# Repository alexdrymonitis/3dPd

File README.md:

# 3dPd

This repository hosts the code, schematics, and circuit board designs made in Kicad, for a hardware digital modular synthesizer. The audio is programmed in Pure Data and the hardware control in the Arduino language.
This synthesizer is supposed to run on a Raspberry Pi 3 and a Teensy3.2. You're welcome to use any other hardware you like, but this specific hardware is supported and explained here.

## Note about the Arduino code

Go to the Arduino_code directory and read the README.txt file first. That should give you enough information about the Arduino code. Do that before you start reading the Pd patches.

## Note about the Pd patches

The heart of this project is the modular_synthesizer.pd patch. Open it and you'll see some other abstractions in there. Go into the [pd modules] sub-patch and look inside.
Each module must have its own abstraction. There are some tutorial module abstractions which show you how to build your own. Open them and read them carefully.

There's also a debug.pd patch which helps with debugging by showing input from the Teensy and printing various message concerning module connections and LED states.

### Dependencies

This project uses the following external libraries:  
zexy  
comport  
iemmatrix  
iemguts  
ggee  
list-abs  
tabreceive_mult~  

The first five libraries are being installed with "apt-get" and the last two are installed through Deken (In Pd got to Help -> Find externals and type these two names -one at a time-, the highlighted version(s) is good for your system).

Pd-0.47.0 or higher is required.

## General note

I'll upload a wiki with instructions for creating the hardware of a module and the whole system. It's in my TODO list, which will hopefully happen in the near future.
You can watch a demo video of the synthesizer here https://www.youtube.com/watch?v=HD13bDPyBWA

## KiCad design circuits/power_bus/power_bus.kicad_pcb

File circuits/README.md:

# Circuit designs, schematics, and gerber files directory

This README file provides only very basic information about the circuits. I'm planning on releasing a wiki on how to build hardware modules in the next few days.

## Generic note about this directory

In this directory you'll find all the circuits used in this modular synthesizer. It's six circuits in total, each in its own directory. They have been designed in Kicad and all the necessary files are here. Each directory includes a README file which states which extra built-in libraries have been used. The ones I have made especially for these circuits are not mentioned in the README since their directories (library/ and .pretty/) are included here. The directories also include the gerber files for sending them to a manufacturer, plus a .png file for each side (in case of double-sided boards) in case you want to DIY etch it, and a .pdf with the schematic.

If you've never used Kicad before and want to modify any of the circuits, I recommend to read some of the tutorials provided from Kicad's website. This tutorial was very useful for me http://kicad-pcb.org/help/documentation/#_getting_started. If you just want to have them manufactured, you can send the gerber files straight to a manufacturer.

## Note about the circuits

### Parts

There's a parts list in every circuit directory with all the parts of that circuit. Where I thought it was necessary, I provide a link to the datasheet of that part. Parts are identified by their annotation from the schematic. Consult the board design (Pcbnew) to make sure which part goes where.

### Orientation of parts

The orientation of the ICs on the "module_generic_top_board" is not defined by the shape of the footprint part but by the pin numbering. If you're not sure, open Pcbnew, go to View -> 3D Viewer and there you can see the notches of the ICs which indicate their orientation.
The orientation of the IDC connectors can be defined by the pin numbering. On an actual IDC connector, you can see a small arrow at the left side of the notch. This arrow indicates that the left-most pin on the side of the notch, is pin number 1.

### Concerning manufacturing

The boards "module_generic_top_board" and "module_generic_bottom_board" are needed for every module. I would suggest to order these from a manufacturer instead of etching them your self many times. The "module_specific_board" and "module_specific_board"2 are just examples of how you can connect your parts to the generic boards (this will be analyzed in the upcoming wiki). There are two of those because I wanted to provide both orientations for the potentiometers, because of the knobs one can find (they are D-shaped knobs, so orientation is rather important). You can order few of these as well, since it is designed in such a way that can host many different layouts.

The "power_bus", "power_distributor", and "teensy_motherboard" are designed as single-side circuit boards (with the "teensy_motherboard" using three jumpers, the "power_bus" only one, and the "power_distributor" none) so that it's easier to etch them yourself. You'll need only one per board (unless you want to build more than 16 modules, then you'll need a second "power_bus", explained in the upcoming wiki), so ordering those from a manufacturer might not work out.

Eacn board has a .pdf file which you can print for DIY etching, either with toner transfer or with photo-resistant boards. The "module_generic_top_board", "module_generic_bottom_board", and "module_specific_board" have two .pdf, one for each side, while the rest three have only one .pdf file.

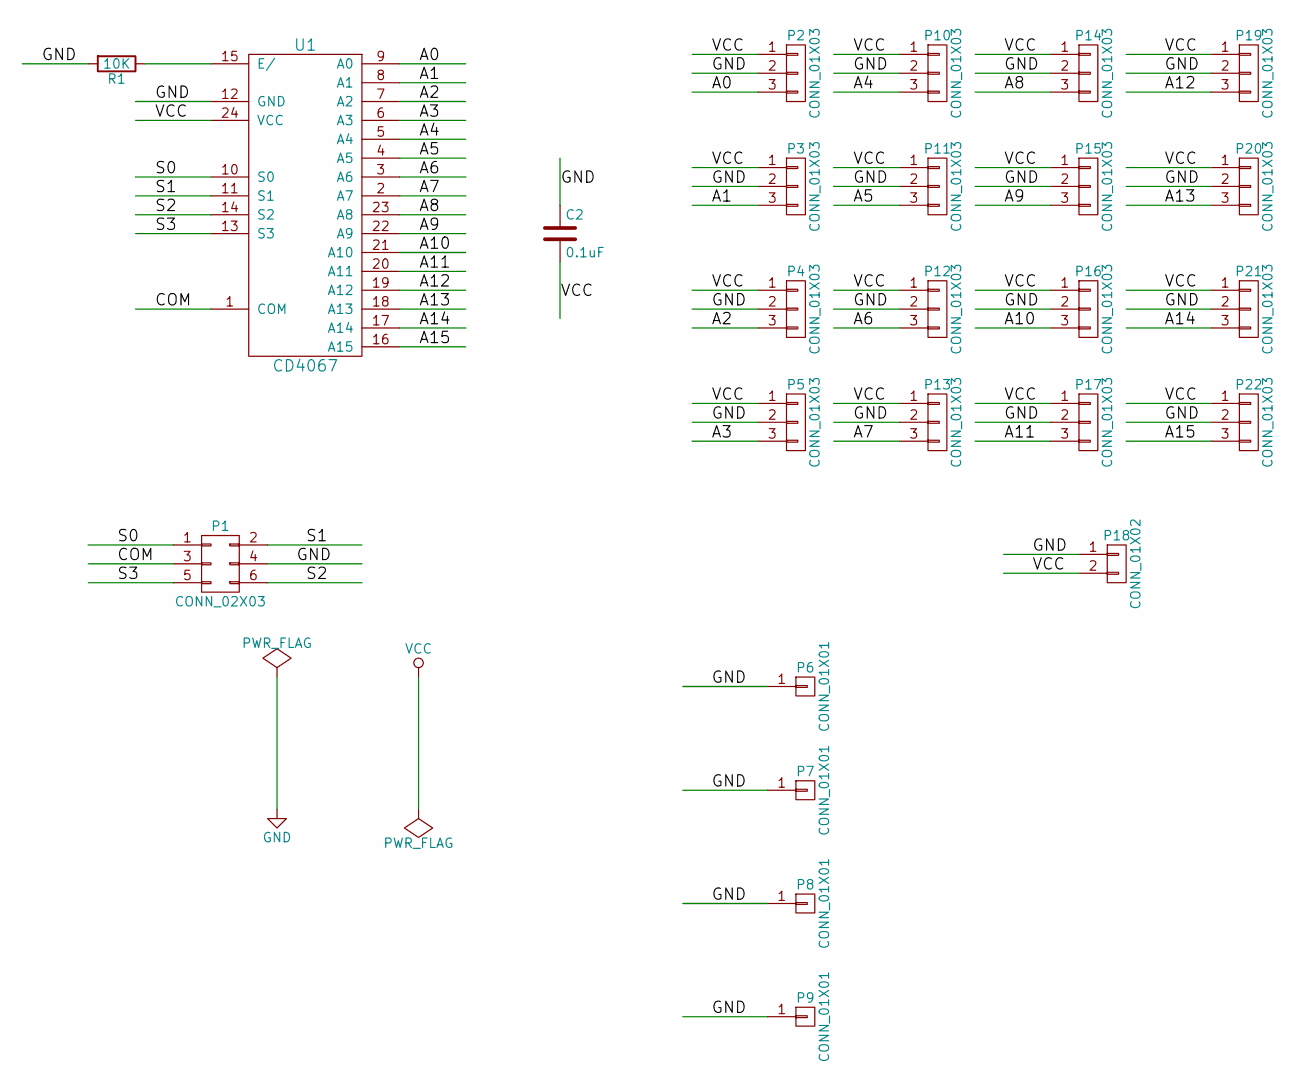
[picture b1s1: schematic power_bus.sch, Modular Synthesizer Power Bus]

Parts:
C2: 0.1uF; C_Disc_D3_P2.5
P1: CONN_02X03; Pin_Header_Straight_2x03
P2, P3, P4, P5, P10, P11, P12, P13, P14, P15, P16, P17, P19, P20, P21, P22: CONN_01X03; Connectors_JST_B3B-PH-K
P6, P7, P8, P9: CONN_01X01; hole
P18: CONN_01X02; bornier2
R1: 10K; R3
U1: CD4067

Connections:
/A0: P2.3, U1.9 (A0)
/A1: P3.3, U1.8 (A1)
/A2: P4.3, U1.7 (A2)
/A3: P5.3, U1.6 (A3)
/A4: P10.3, U1.5 (A4)
/A5: P11.3, U1.4 (A5)
/A6: P12.3, U1.3 (A6)
/A7: P13.3, U1.2 (A7)
/A8: P14.3, U1.23 (A8)
/A9: P15.3, U1.22 (A9)
/A10: P16.3, U1.21 (A10)
/A11: P17.3, U1.20 (A11)
/A12: P19.3, U1.19 (A12)
/A13: P20.3, U1.18 (A13)
/A14: P21.3, U1.17 (A14)
/A15: P22.3, U1.16 (A15)
/COM: P1.3, U1.1 (COM)
/S0: P1.1, U1.10 (S0)
/S1: P1.2, U1.11 (S1)
/S2: P1.6, U1.14 (S2)
/S3: P1.5, U1.13 (S3)
GND: C2.1, P1.4, P2.2, P3.2, P4.2, P5.2, P6.1, P7.1, P8.1, P9.1, P10.2, P11.2, P12.2, P13.2, P14.2, P15.2, P16.2, P17.2, P18.1, P19.2, P20.2, P21.2, P22.2, R1.2, U1.12 (GND)
unnamed: R1.1, U1.15 (E‭‎/)
VCC: C2.2, P2.1, P3.1, P4.1, P5.1, P10.1, P11.1, P12.1, P13.1, P14.1, P15.1, P16.1, P17.1, P18.2, P19.1, P20.1, P21.1, P22.1, U1.24 (VCC)

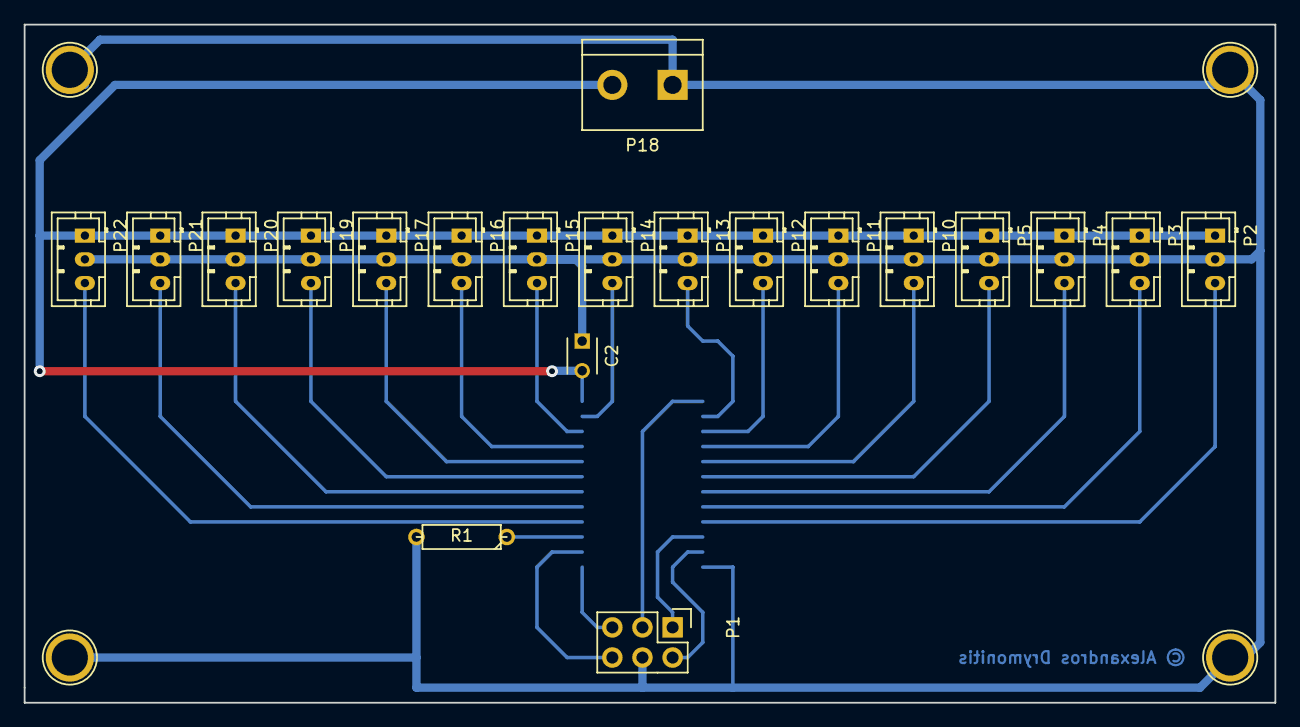
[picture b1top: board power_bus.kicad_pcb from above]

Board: 2 copper layers, 105.4 x 57.2 mm, 25 parts (1 on the bottom side), 24 nets.

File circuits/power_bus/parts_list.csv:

Reference, Value, Type, Datasheet
U1,CD4067,16-channel Analog Multiplexer 4067,https://www.sparkfun.com/datasheets/IC/CD74HC4067.pdf
P2,CONN_01X03,JST PH Connector Male Angled 3-pin,
P10,CONN_01X03,JST PH Connector Male Angled 3-pin,
P14,CONN_01X03,JST PH Connector Male Angled 3-pin,
P19,CONN_01X03,JST PH Connector Male Angled 3-pin,
P3,CONN_01X03,JST PH Connector Male Angled 3-pin,
P11,CONN_01X03,JST PH Connector Male Angled 3-pin,
P15,CONN_01X03,JST PH Connector Male Angled 3-pin,
P20,CONN_01X03,JST PH Connector Male Angled 3-pin,
P4,CONN_01X03,JST PH Connector Male Angled 3-pin,
P12,CONN_01X03,JST PH Connector Male Angled 3-pin,
P16,CONN_01X03,JST PH Connector Male Angled 3-pin,
P21,CONN_01X03,JST PH Connector Male Angled 3-pin,
P5,CONN_01X03,JST PH Connector Male Angled 3-pin,
P13,CONN_01X03,JST PH Connector Male Angled 3-pin,
P17,CONN_01X03,JST PH Connector Male Angled 3-pin,
P22,CONN_01X03,JST PH Connector Male Angled 3-pin,
P1,CONN_02X03,IDC Connector Male 2x3 Straight,
C2,0.1uF,Capacitor Ceramic Unpolarized,
P18,CONN_01X02,Screw Terminal 2-pin 5mm Pitch,
R1,10K,Resistor,

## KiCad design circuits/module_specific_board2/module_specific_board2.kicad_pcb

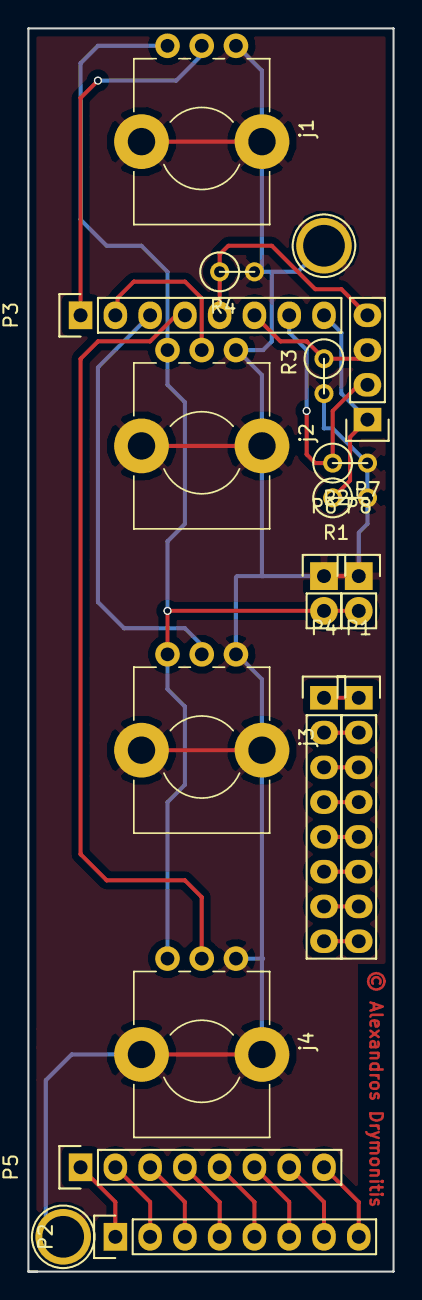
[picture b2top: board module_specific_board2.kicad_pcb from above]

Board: 2 copper layers, 26.7 x 90.8 mm, 18 parts (0 on the bottom side), 26 nets.

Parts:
P1, P2, P3, P4, P5: CONN_01X08; Pin_Header_Straight_1x08
P6, P8: CONN_01X02; Pin_Header_Straight_1x02
P7: CONN_01X04; Pin_Header_Straight_1x04
P9, P10: CONN_01X01; hole
R1, R2, R3, R4: 10K; R1
j1, j2, j3, j4: ALPSpot097; Potentiometer_Alps_RK09K_Horizontal

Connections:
/MUX5: P3.5, P7.4, R4.1
/MUX6: P3.6, P7.3, R3.1
/MUX7: P3.7, P7.2, R2.1
/MUX8: P3.8, P7.1, R1.1
/POT1: P3.1, j1.2
/POT2: P3.2, j2.2
/POT3: P3.3, j3.2
/POT4: P3.4, j4.2
GND: P6.1, P8.1, P9.1, P10.1, R1.2, R2.2, R3.2, R4.2, j1.0, j1.3, j2.0, j2.3, j3.0, j3.3, j4.0, j4.3
unnamed: P1.1, P4.1
unnamed: P1.2, P4.2
unnamed: P1.3, P4.3
unnamed: P1.4, P4.4
unnamed: P1.5, P4.5
unnamed: P1.6, P4.6
unnamed: P1.7, P4.7
unnamed: P1.8, P4.8
unnamed: P2.1, P5.1
unnamed: P2.2, P5.2
unnamed: P2.3, P5.3
unnamed: P2.4, P5.4
unnamed: P2.5, P5.5
unnamed: P2.6, P5.6
unnamed: P2.7, P5.7
unnamed: P2.8, P5.8
VCC: P6.2, P8.2, j1.1, j2.1, j3.1, j4.1

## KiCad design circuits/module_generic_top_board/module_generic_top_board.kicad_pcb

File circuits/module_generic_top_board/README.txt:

This circuit contains the Connectors_JST_PH.pretty footprint library in the project specific libraries, from ${KISYSMOD}/Connectors_JST_PH.pretty

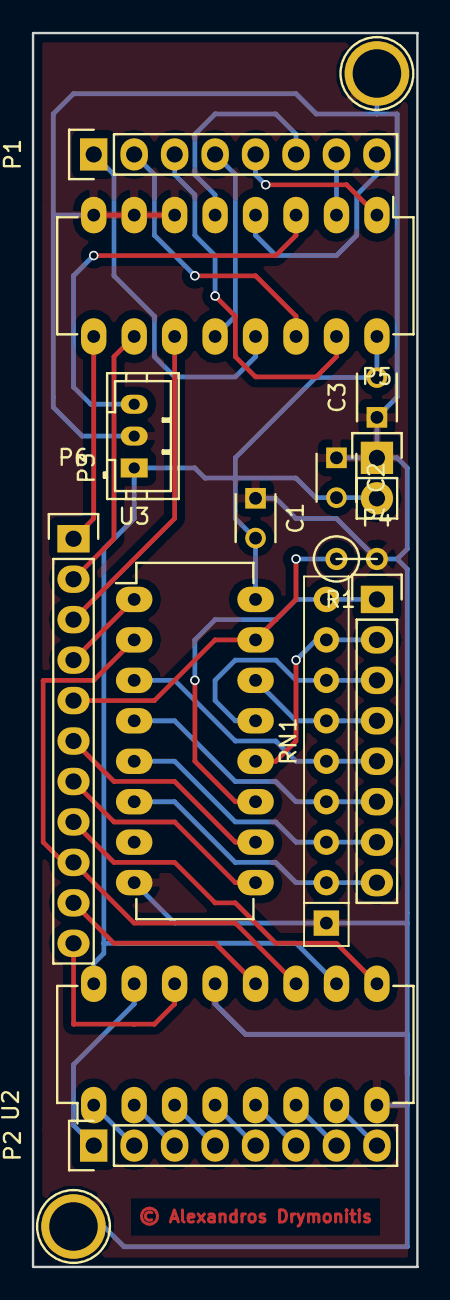
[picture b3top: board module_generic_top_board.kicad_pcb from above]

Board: 2 copper layers, 24.1 x 77.5 mm, 16 parts (0 on the bottom side), 38 nets.

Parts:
C1, C2, C3: 0.1uF; C_Disc_D3_P2.5
P1, P2, P4: CONN_01X08; Pin_Header_Straight_1x08
P3: CONN_01X03; Connectors_JST_B3B-PH-K
P5: CONN_01X02; Pin_Header_Straight_1x02
P6: CONN_01X11; Pin_Header_Straight_1x11
P7, P8: CONN_01X01; hole
R1: 10K; R1
RN1: 10K; R_Array_SIP9
U1: 4051; DIP-16_W7.62mm_LongPads
U2: 74HC595; DIP-16_W7.62mm_LongPads
U3: 74HC165; DIP-16_W7.62mm_LongPads

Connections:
/MUXA: P6.3, U1.11
/MUXB: P6.2, U1.10
/MUXC: P6.1, U1.9
/QH: P6.7, U3.9
/QH/: P6.8, U2.9
/RCLK: P6.10, U2.12
/SH/LD: P6.4, U3.1
/SHIFTIN_A: P4.1, RN1.9, U3.11
/SHIFTIN_B: P4.2, RN1.8, U3.12
/SHIFTIN_C: P4.3, RN1.7, U3.13
/SHIFTIN_D: P4.4, RN1.6, U3.14
/SHIFTIN_E: P4.5, RN1.5, U3.3
/SHIFTIN_F: P4.6, RN1.4, U3.4
/SHIFTIN_G: P4.7, RN1.3, U3.5
/SHIFTIN_H: P4.8, RN1.2, U3.6
/SHIFTIN_SER: P6.6, U3.10
/SHIFTOUT_SER: P6.11, U2.14
/SHIFT_INH: P6.5, R1.1, U3.15
/SRCLK: P6.9, U2.11, U3.2
GND: C1.1, C2.1, C3.1, P3.2, P5.1, P7.1, P8.1, R1.2, RN1.1, U1.6, U1.7, U1.8, U2.8, U2.13, U3.8
unnamed: P1.1, U1.13
unnamed: P1.2, U1.14
unnamed: P1.3, U1.15
unnamed: P1.4, U1.12
unnamed: P1.5, U1.1
unnamed: P1.6, U1.5
unnamed: P1.7, U1.2
unnamed: P1.8, U1.4
unnamed: P2.1, U2.15
unnamed: P2.2, U2.1
unnamed: P2.3, U2.2
unnamed: P2.4, U2.3
unnamed: P2.5, U2.4
unnamed: P2.6, U2.5
unnamed: P2.7, U2.6
unnamed: P2.8, U2.7
unnamed: P3.3, U1.3
VCC: C1.2, C2.2, C3.2, P3.1, P5.2, U1.16, U2.10, U2.16, U3.16

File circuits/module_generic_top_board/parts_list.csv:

Reference, Value,Type, Datasheet
C1,0.1uF,Capacitor Ceramic Unpolarized,
C2,0.1uF,Capacitor Ceramic Unpolarized,
C3,0.1uF,Capacitor Ceramic Unpolarized,
RR1,10K,Resistor Network 8 + 1,
P2,CONN_01X08,Female Header Straight 8-pin 0.1 Inch,
P1,CONN_01X08,Female Header Straight 8-pin 0.1 Inch,
P4,CONN_01X08,Female Header Straight 8-pin 0.1 Inch,
P5,CONN_01X02,Female Header Straight 2-pin 0.1 Inch,
P6,CONN_01X11,Female Header Straight 11-pin 0.1 Inch,
P3,CONN_01X03,JST PH Connector Male Angled 3-pin,
U3,74HC165,8-bit Input Shift Register,https://cdn.sparkfun.com/datasheets/BreakoutBoards/sn54hc165.pdf
U2,74HC595,8-bit Output Shift Register,http://www.ti.com/lit/ds/symlink/sn74hc595.pdf
U1,4051,8-channel Analog Multiplexer,http://grobotronics.com/images/datasheets/schs354a.pdf
R1,10K,Resistor,

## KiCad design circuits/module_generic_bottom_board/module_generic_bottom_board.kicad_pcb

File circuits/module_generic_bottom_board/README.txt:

This circuit contains the switches schematic parts library from /usr/share/kicak/library

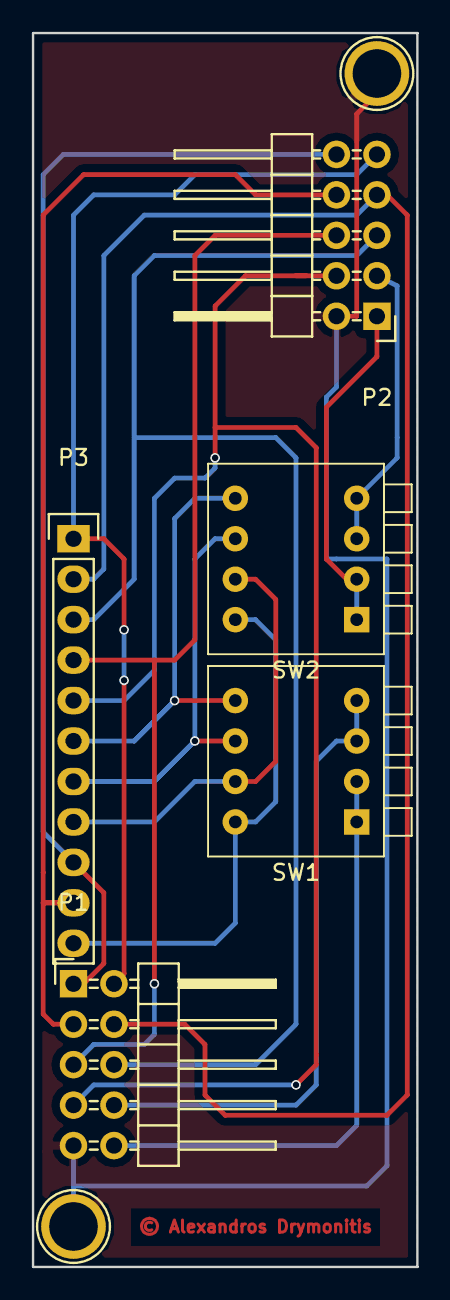
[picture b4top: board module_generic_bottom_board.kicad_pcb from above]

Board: 2 copper layers, 24.1 x 77.5 mm, 7 parts (0 on the bottom side), 16 nets.

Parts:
P1, P2: CONN_02X05; Pin_Header_Angled_2x05
P3: CONN_01X11; Pin_Header_Straight_1x11
P4, P5: CONN_01X01; hole
SW1, SW2: SW_DIP_x04; SW_DIP_x4_W7.62mm_Piano

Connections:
/MUXA: P1.6, P2.5, P3.3
/MUXB: P1.4, P2.7, P3.2
/MUXC: P1.2, P2.9, P3.1
/QH: P3.7, SW1.6, SW2.6
/QH/: P3.8, SW1.7, SW2.7
/RCLK: P1.3, P2.8, P3.10
/SH/LD: P1.5, P2.6, P3.4
/SHIFTIN_SER: P3.6, SW1.5, SW2.5
/SHIFTOUT_SER: P3.11, SW1.8, SW2.8
/SHIFT_INH: P1.7, P2.4, P3.5
/SRCLK: P1.1, P2.10, P3.9
/SW1_12: P1.10, SW1.1, SW1.2
/SW1_34: P1.8, SW1.3, SW1.4
/SW2_12: P2.1, SW2.1, SW2.2
/SW2_34: P2.3, SW2.3, SW2.4
GND: P1.9, P2.2, P4.1, P5.1

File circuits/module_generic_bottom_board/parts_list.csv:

Reference, Value, Type
P2,CONN_02X05,IDC Connector 2x5 Angled
P1,CONN_02X05,IDC Connector 2x5 Angled
P3,CONN_01X11,Header Male 11-pin Straight
S1,SW_DIP_x4,DIP Switch 4-position Piano Type
S2,SW_DIP_x4,DIP Switch 4-position Piano Type

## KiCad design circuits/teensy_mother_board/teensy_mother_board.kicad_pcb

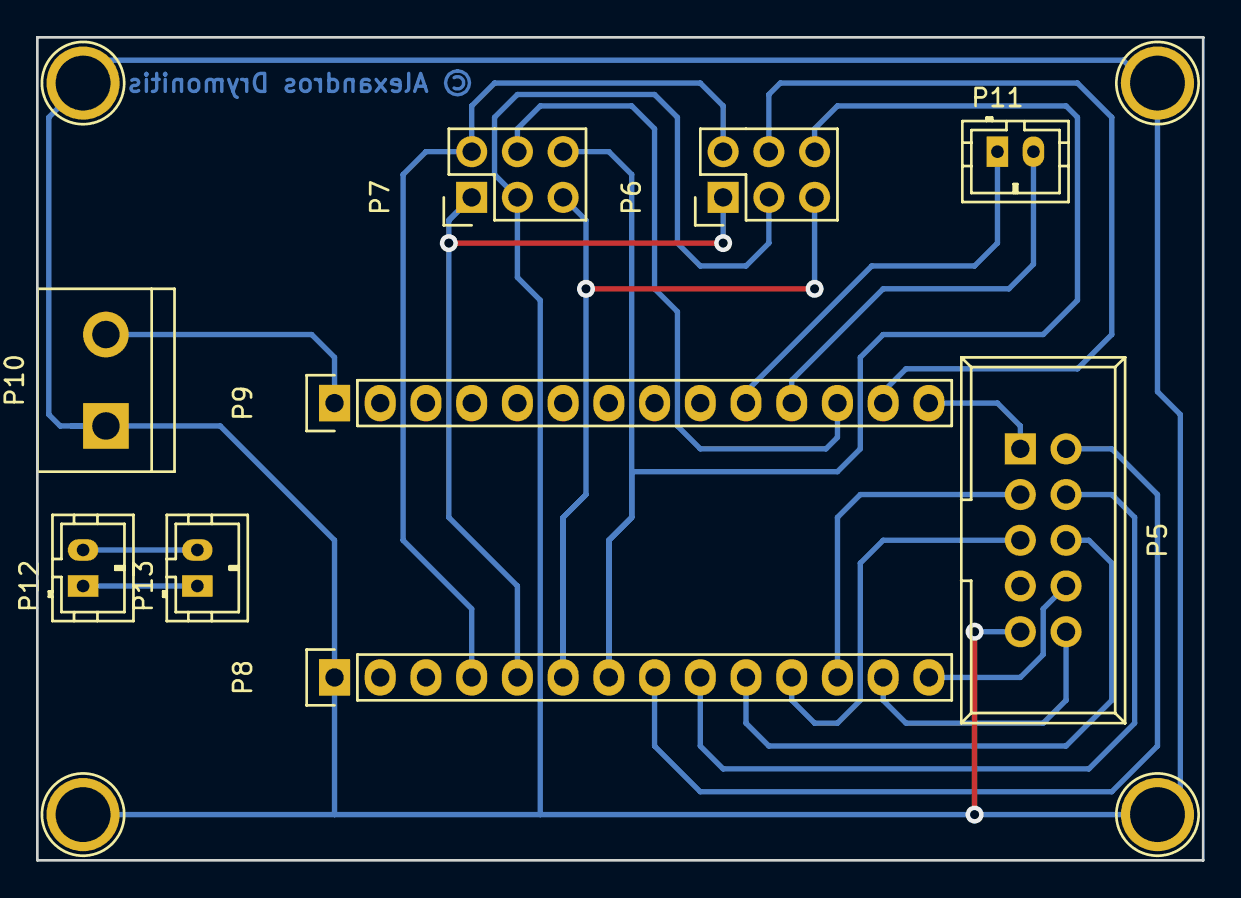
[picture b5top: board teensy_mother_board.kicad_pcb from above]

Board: 2 copper layers, 64.8 x 45.7 mm, 13 parts (0 on the bottom side), 20 nets.

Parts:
P1, P2, P3, P4: CONN_01X01; hole
P5: CONN_02X05; IDC_Header_Straight_10pins
P6, P7: CONN_02X03; Pin_Header_Straight_2x03
P8, P9: CONN_01X14; Pin_Header_Straight_1x14
P10: CONN_01X02; bornier2
P11, P12, P13: CONN_01X02; Connectors_JST_B2B-PH-K

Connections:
/ANALOG_IN_A: P6.4, P9.13
/ANALOG_IN_B: P7.4, P9.12
/CONST_HIGH: P9.11, P11.2
/D+: P12.1, P13.1
/D-: P12.2, P13.2
/INPUT_LATCH: P5.5, P8.11
/INTERRUPT: P9.10, P11.1
/MASTER_MUX_A: P6.6, P7.6, P8.7
/MASTER_MUX_B: P6.5, P7.5, P8.6
/MASTER_MUX_C: P6.1, P7.1, P8.5
/MASTER_MUX_D: P6.2, P7.2, P8.4
/MISO: P5.8, P8.14
/MOSI: P5.10, P8.13
/OUTPUT_LATCH: P5.3, P8.12
/SCK: P5.1, P9.14
/SLAVE_MUX_A: P5.6, P8.10
/SLAVE_MUX_B: P5.4, P8.9
/SLAVE_MUX_C: P5.2, P8.8
GND: P1.1, P2.1, P3.1, P4.1, P5.9, P6.3, P7.3, P8.1, P10.1
VCC: P9.1, P10.2

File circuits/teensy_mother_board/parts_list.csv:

Reference, Value, Footprint
P9,CONN_01X14,Header Male 14-pin Straight (to host Teensy)
P8,CONN_01X14,Header Male 14-pin Straight (to host Teensy)
P5,CONN_02X05,IDC Connector Male 2x5 Straight
P6,CONN_02X03,IDC Connector Male 2x3 Straight
P7,CONN_02X03,IDC Connector Male 2x3 Straight
P10,CONN_01X02,Screw Terminal 2-pin 5mm Pitch
P11,CONN_01X02,JST PH Connector Male Angled 2-pin
P13,CONN_01X02,JST PH Connector Male Angled 2-pin
P12,CONN_01X02,JST PH Connector Male Angled 2-pin

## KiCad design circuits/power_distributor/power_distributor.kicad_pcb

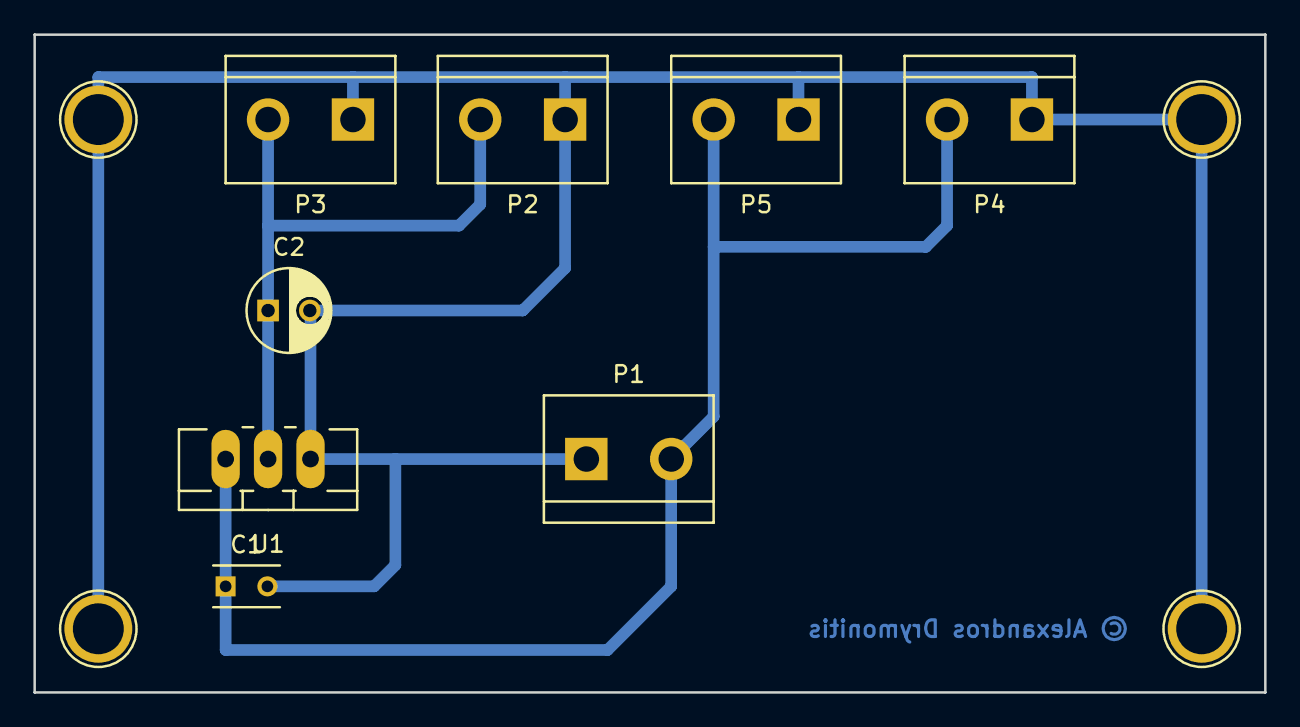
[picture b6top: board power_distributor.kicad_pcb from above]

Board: 2 copper layers, 73.7 x 39.4 mm, 12 parts (0 on the bottom side), 3 nets.

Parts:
C1: 100nF; C_Rect_L4_W2.5_P2.5
C2: 10uF; C_Radial_D5_L6_P2.5
P1, P2, P3, P4, P5: CONN_01X02; bornier2
P6, P7, P8, P9: CONN_01X01; hole
U1: LD1117S33TR; TO-220_Neutral123_Vertical_LargePads

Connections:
/VO: C2.1, P2.2, P3.2, U1.2
GND: C1.2, C2.2, P1.1, P2.1, P3.1, P4.1, P5.1, P6.1, P7.1, P8.1, P9.1, U1.1
VCC: C1.1, P1.2, P4.2, P5.2, U1.3

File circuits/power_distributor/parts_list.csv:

Reference, Value, Footprint, Datasheet
P1,CONN_01X02,Screw Temrinal 2-pin 5mm Pitch,
P2,CONN_01X02,Screw Temrinal 2-pin 5mm Pitch,
P3,CONN_01X02,Screw Temrinal 2-pin 5mm Pitch,
P4,CONN_01X02,Screw Temrinal 2-pin 5mm Pitch,
P5,CONN_01X02,Screw Temrinal 2-pin 5mm Pitch,
U1,LD1117S33TR,Voltage Regulator LD1117 - 3.3V 800mA,http://grobotronics.com/images/datasheets/ld1117.pdf
C1,100nF,Capacitor Ceramic Unpolarized,
C2,10uF,Capacitor Electrolytic Polarized,

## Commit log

2016-08-11 minor corrections
2016-08-11 added circuit schematics and desings
2016-08-11 update abstractions
2016-08-11 update generic abstractions
2016-08-12 Update main patch
2016-08-12 Update [template_module~]
2016-08-12 Update [get_switches]
2016-08-12 Update [accumulate_connections]
2016-11-18 Update [arduino_data] abstraction
2016-11-18 Fixed smoothing issue in Arduino code
2016-11-18 Update analog smoothing
2017-06-11 added [module_input~]
2017-06-11 added [module_output~]
2017-06-11 added [input_state]
2017-06-11 added [output_state]
2017-07-01 Update Arduino sketches
2017-07-01 Update Pd Patches
2017-07-17 Include schematic .pdf files
2017-07-17 Update Arduino code
2017-07-19 Update envelope tutorial patch
2017-08-16 Update module specific board
2017-08-16 Replaced PNGs with PDFs
2017-08-16 Update PDF files
2017-09-01 Update patches and sketches
2017-09-01 removed alias module abstraction
2017-09-01 Update debug patch
2017-09-02 Update [module_data]
2017-09-02 Update [matrix_connections]
2017-09-03 Update 13-bug fix abstractions
2017-09-03 Update 13-bug fix code
2017-09-03 Update [arduino_data13]
2017-09-04 Update gerber files
2017-09-04 Update module_generic_bottom_board
2017-09-04 removed cache.lib file
2017-09-04 Update module template
2017-09-05 Update [module_input~]
2017-09-07 Update parts list
2017-09-10 Add [activity_ctl]
2017-09-10 Added tutorial_use_actinity_ctl.pd
2017-10-02 Update [module_output~]
2017-10-24 Update circuits
2017-10-24 Added Module Specific Board 2
2017-10-24 Update Module Generic Top Board

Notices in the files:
circuits/module_generic_bottom_board/module_generic_bottom_board.kicad_pcb:
© Alexandros Drymonitis
